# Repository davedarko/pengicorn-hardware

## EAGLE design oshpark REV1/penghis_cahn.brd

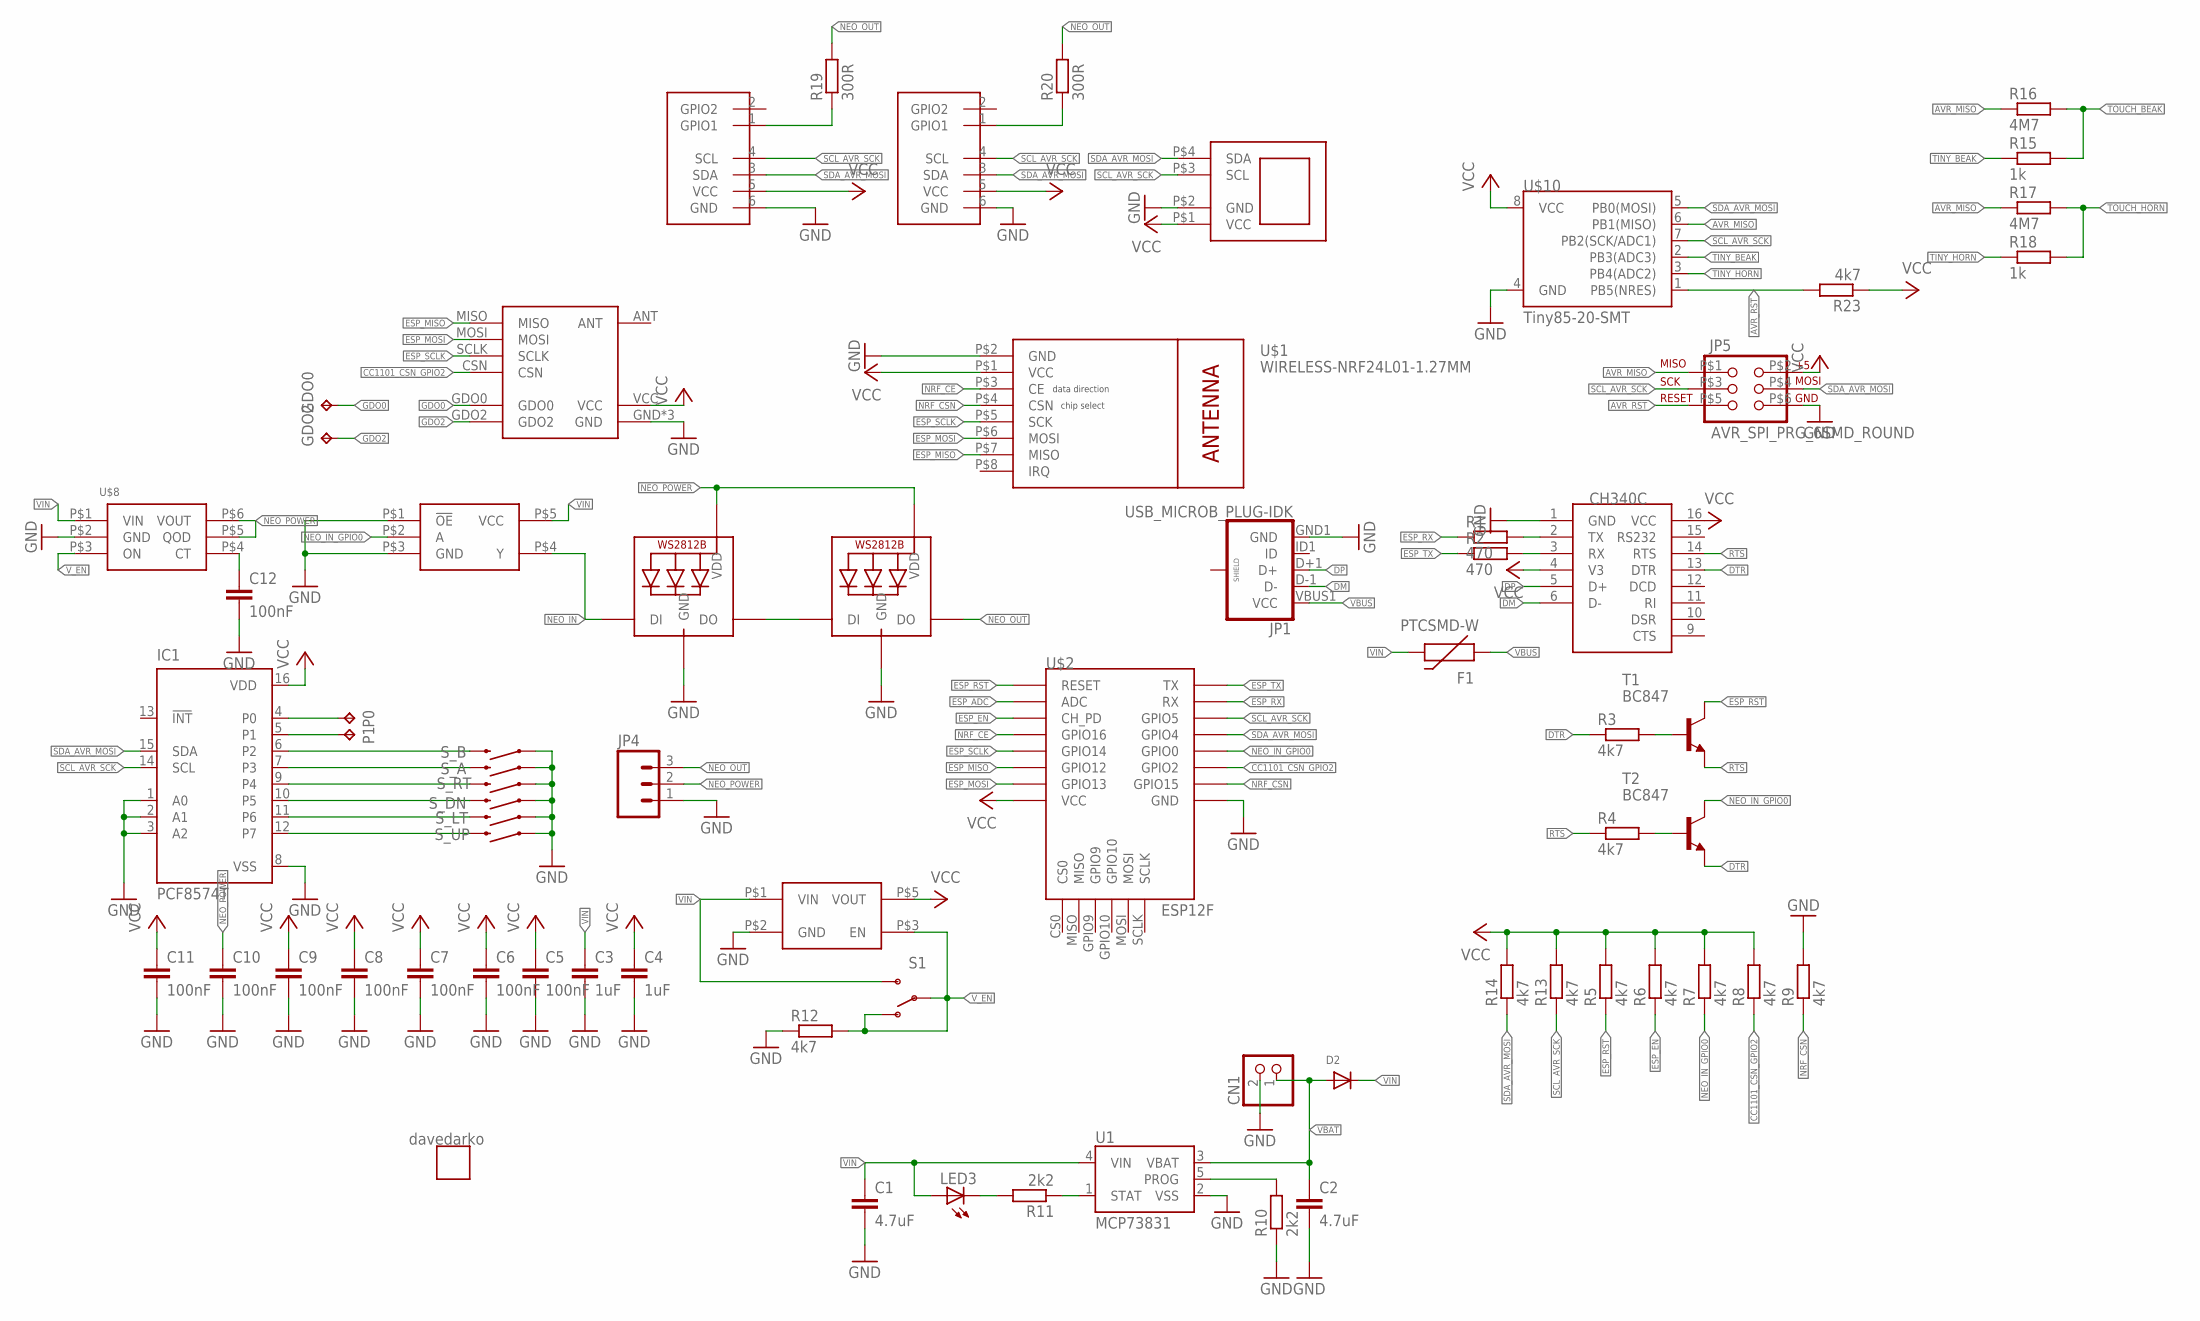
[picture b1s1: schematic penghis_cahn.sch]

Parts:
C1, C2: 4.7uF; C0805
C3, C4: 1uF; C0805
C5, C6, C7, C8, C9, C10, C11, C12: 100nF; C0805
CN1: JST_2PIN-SMT-RA; JST-PH-2-SMT-RA
D2: DIODESOD-123; SOD-123
F1: PTCSMD-W; PTC-1206-WIDE
GDO0, GDO2: TPB1,27; B1,27
IC1: PCF8574T; SO16W
JP1: USB_MICROB_PLUG-IDK; USB-AB-MICRO-SMD_SLOT
JP4: M03LOCK; 1X03_LOCK
JP5: AVR_SPI_PRG_6SMD_ROUND; 2X3_SMD_PAD_ROUND
LED1, LED2: WS2812B5050; WS2812B
LED3: LEDCHIP-LED0603; CHIP-LED0603
P0, P1: TPB1,27; B1,27
R1, R2: 470; R0603
R3, R4, R5, R6, R7, R8, R9, R12, R13, R14, R23: 4k7; R0603
R10, R11: 2k2; R0603
R15, R18: 1k; R0603
R16, R17: 4M7; R0603
R19, R20: 300R; R0603
S1: SWITCH-SPDT-SMD-A; SWITCH-SPST-SMD-A
SAO1, SAO2: SAO-SHITTY-ADDONMASTER; 2X3-KEYED-FEMALE
S_A: SWITCH-MOMENTARY-2-SMD-1101NE; TACTILE-SWITCH-1101NE
S_B: SWITCH-MOMENTARY-2-SMD-1101NE; TACTILE-SWITCH-1101NE
S_DN: SWITCH-MOMENTARY-2-SMD-1101NE; TACTILE-SWITCH-1101NE
S_LT: SWITCH-MOMENTARY-2-SMD-1101NE; TACTILE-SWITCH-1101NE
S_RT: SWITCH-MOMENTARY-2-SMD-1101NE; TACTILE-SWITCH-1101NE
S_UP: SWITCH-MOMENTARY-2-SMD-1101NE; TACTILE-SWITCH-1101NE
T1, T2: BC847; SOT23
U1: MCP73831; SOT23-5
U$1: WIRELESS-NRF24L01-1.27MM
U$2: ESP12F; ESP12PAD
U$3: AP2112KAP2112K; AP2112
U$4: CH340CCH340C; SOIC16
U$5: SN74LV1T125; SN74LV1T125DBVR
U$6: CC1101
U$7: OLED_I2C_VGCD; OLED_1.3
U$8: TPS22917; SOT23
U$9: DAVEDARKODDGOLD; DAVEDARKO_GOLD
U$10: Tiny85-20-SMT; SO08-EIAJ

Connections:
AVR_MISO: JP5.P$1 (1), R16.1, R17.1, U$10.6 (PB1(MISO))
AVR_RST: JP5.P$5 (5), R23.2, U$10.1 (PB5(NRES))
CC1101_CSN_GPIO2: R8.1, U$2.GPIO2, U$6.CSN
DM: JP1.D-1 (D-), U$4.6 (D-)
DP: JP1.D+1 (D+), U$4.5 (D+)
DTR: R3.1, T2.2 (E), U$4.13 (DTR)
ESP_ADC: U$2.ADC
ESP_EN: R6.1, U$2.EN (CH_PD)
ESP_MISO: U$1.P$7 (MISO), U$2.GPIO12, U$6.MISO
ESP_MOSI: U$1.P$6 (MOSI), U$2.GPIO13, U$6.MOSI
ESP_RST: R5.1, T1.3 (C), U$2.RST (RESET)
ESP_RX: R1.1, U$2.RX
ESP_SCLK: U$1.P$5 (SCK), U$2.GPIO14, U$6.SCLK
ESP_TX: R2.1, U$2.TX
GDO0: GDO0.TP, U$6.GDO0
GDO2: GDO2.TP, U$6.GDO2
GND: C1.2, C2.2, C3.2, C4.2, C5.2, C6.2, C7.2, C8.2, C9.2, C10.2, C11.2, C12.2, CN1.2 (1), IC1.1 (A0), IC1.2 (A1), IC1.3 (A2), IC1.8 (VSS), JP1.GND1 (GND), JP4.1, JP5.P$6 (6), LED1.3-GND (GND), LED2.3-GND (GND), R9.2, R10.1, R12.1, SAO1.6 (GND), SAO2.6 (GND), S_A.P$1 (1), S_B.P$1 (1), S_DN.P$1 (1), S_LT.P$1 (1), S_RT.P$1 (1), S_UP.P$1 (1), U1.2 (VSS), U$1.P$2 (GND), U$2.GND, U$3.P$2 (GND), U$4.1 (GND), U$5.P$1 (!OE), U$5.P$3 (GND), U$6.GND, U$6.GND2 (GND), U$6.GND3 (GND), U$7.P$2 (GND), U$8.P$2 (GND), U$10.4 (GND)
unnamed: LED1.2-DOUT (DO), LED2.4-DIN (DI)
unnamed: IC1.12 (P7), S_UP.P$2 (2)
unnamed: IC1.11 (P6), S_LT.P$2 (2)
unnamed: IC1.10 (P5), S_DN.P$2 (2)
unnamed: IC1.9 (P4), S_RT.P$2 (2)
unnamed: R3.2, T1.1 (B)
unnamed: R4.2, T2.1 (B)
unnamed: IC1.7 (P3), S_A.P$2 (2)
unnamed: R19.1, SAO1.1 (GPIO1)
unnamed: R10.2, U1.5 (PROG)
unnamed: R11.1, U1.1 (STAT)
unnamed: R2.2, U$4.3 (RX)
unnamed: R1.2, U$4.2 (TX)
unnamed: IC1.6 (P2), S_B.P$2 (2)
unnamed: LED3.C, R11.2
unnamed: C12.1, U$8.P$4 (CT)
unnamed: R20.1, SAO2.1 (GPIO1)
NEO_IN: LED1.4-DIN (DI), U$5.P$4 (Y)
NEO_IN_GPIO0: R7.1, T2.3 (C), U$2.GPIO0, U$5.P$2 (A)
NEO_OUT: JP4.3, LED2.2-DOUT (DO), R19.2, R20.2
NEO_POWER: C10.1, JP4.2, LED1.1-VDD (VDD), LED2.1-VDD (VDD), U$8.P$5 (QOD), U$8.P$6 (VOUT)
NRF_CE: U$1.P$3 (CE), U$2.GPIO16
NRF_CSN: R9.1, U$1.P$4 (CSN), U$2.GPIO15
P0: IC1.4 (P0), P0.TP
P1: IC1.5 (P1), P1.TP
RTS: R4.1, T1.2 (E), U$4.14 (RTS)
SCL_AVR_SCK: IC1.14 (SCL), JP5.P$3 (3), R13.1, SAO1.4 (SCL), SAO2.4 (SCL), U$2.GPIO5, U$7.P$3 (SCL), U$10.7 (PB2(SCK/ADC1))
SDA_AVR_MOSI: IC1.15 (SDA), JP5.P$4 (4), R14.1, SAO1.3 (SDA), SAO2.3 (SDA), U$2.GPIO4, U$7.P$4 (SDA), U$10.5 (PB0(MOSI))
TINY_BEAK: R15.1, U$10.2 (PB3(ADC3))
TINY_HORN: R18.1, U$10.3 (PB4(ADC2))
TOUCH_BEAK: R15.2, R16.2
TOUCH_HORN: R17.2, R18.2
VBAT: C2.1, CN1.1 (2), D2.A, U1.3 (VBAT)
VBUS: F1.1, JP1.VBUS1 (VCC)
VCC: C4.1, C5.1, C6.1, C7.1, C8.1, C9.1, C11.1, IC1.16 (VDD), JP5.P$2 (2), R5.2, R6.2, R7.2, R8.2, R13.2, R14.2, R23.1, SAO1.5 (VCC), SAO2.5 (VCC), U$1.P$1 (VCC), U$2.VCC, U$3.P$5 (VOUT), U$4.4 (V3), U$4.16 (VCC), U$6.VCC, U$7.P$1 (VCC), U$10.8 (VCC)
VIN: C1.1, C3.1, D2.C, F1.2, LED3.A, S1.3 (S), U1.4 (VIN), U$3.P$1 (VIN), U$5.P$5 (VCC), U$8.P$1 (VIN)
V_EN: R12.2, S1.1 (O), S1.2, U$3.P$3 (EN), U$8.P$3 (ON)

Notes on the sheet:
data direction
chip select

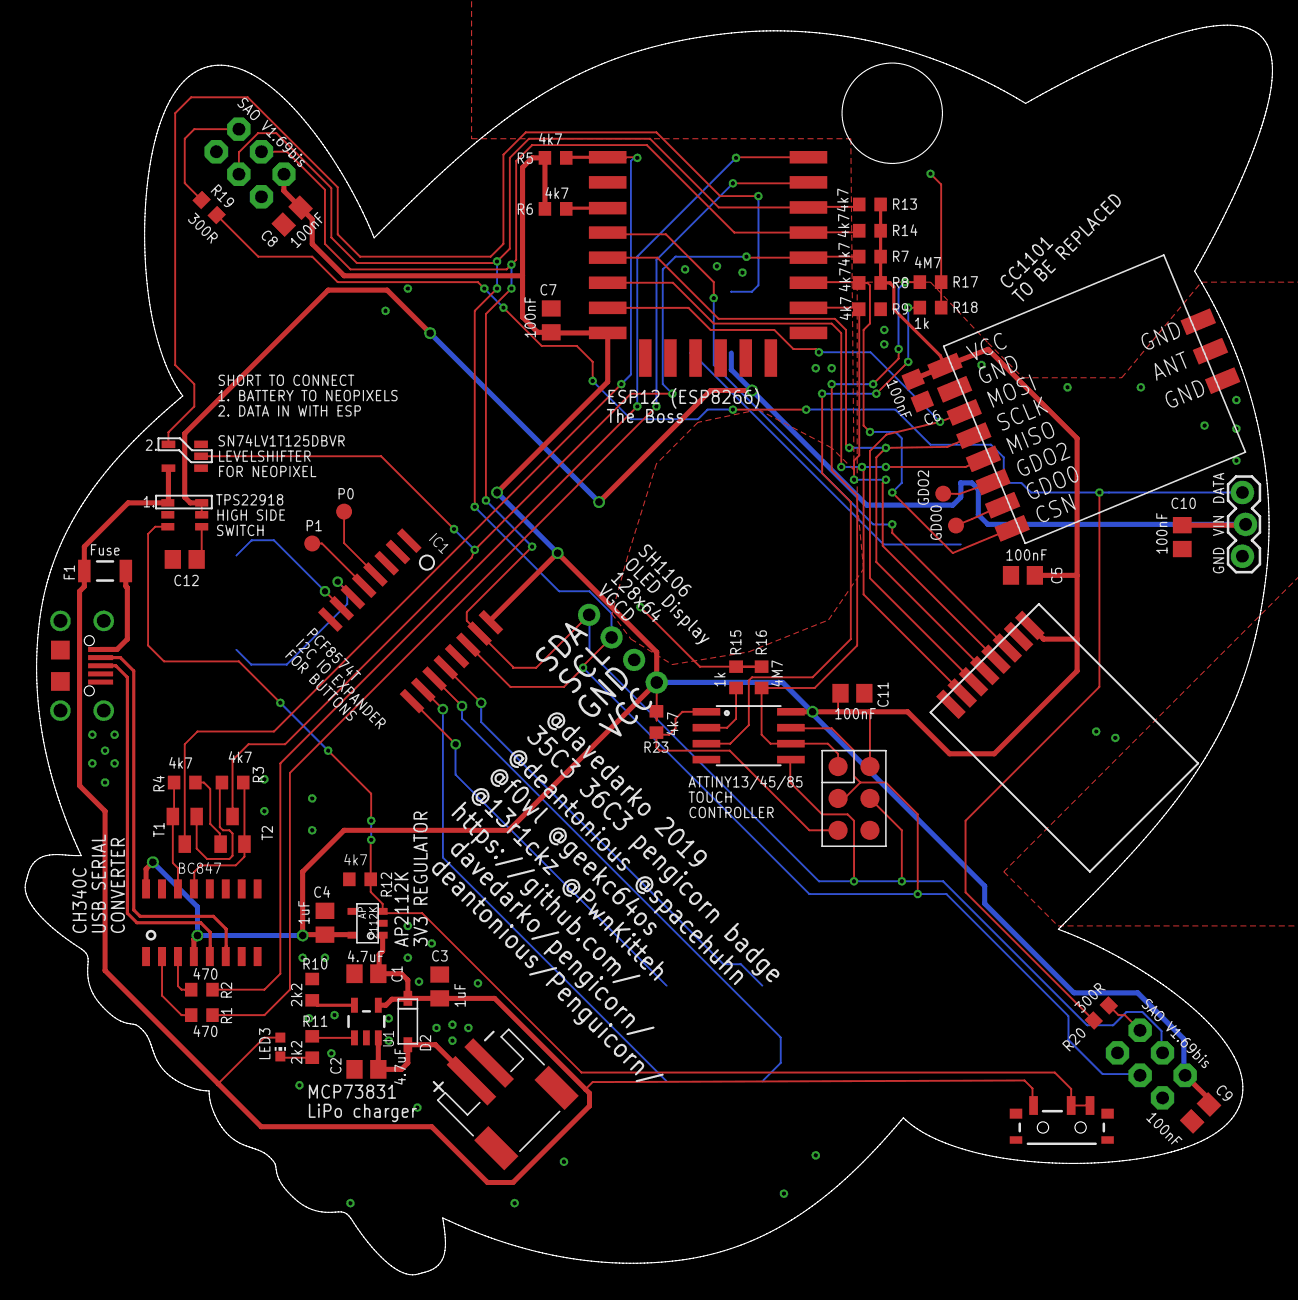
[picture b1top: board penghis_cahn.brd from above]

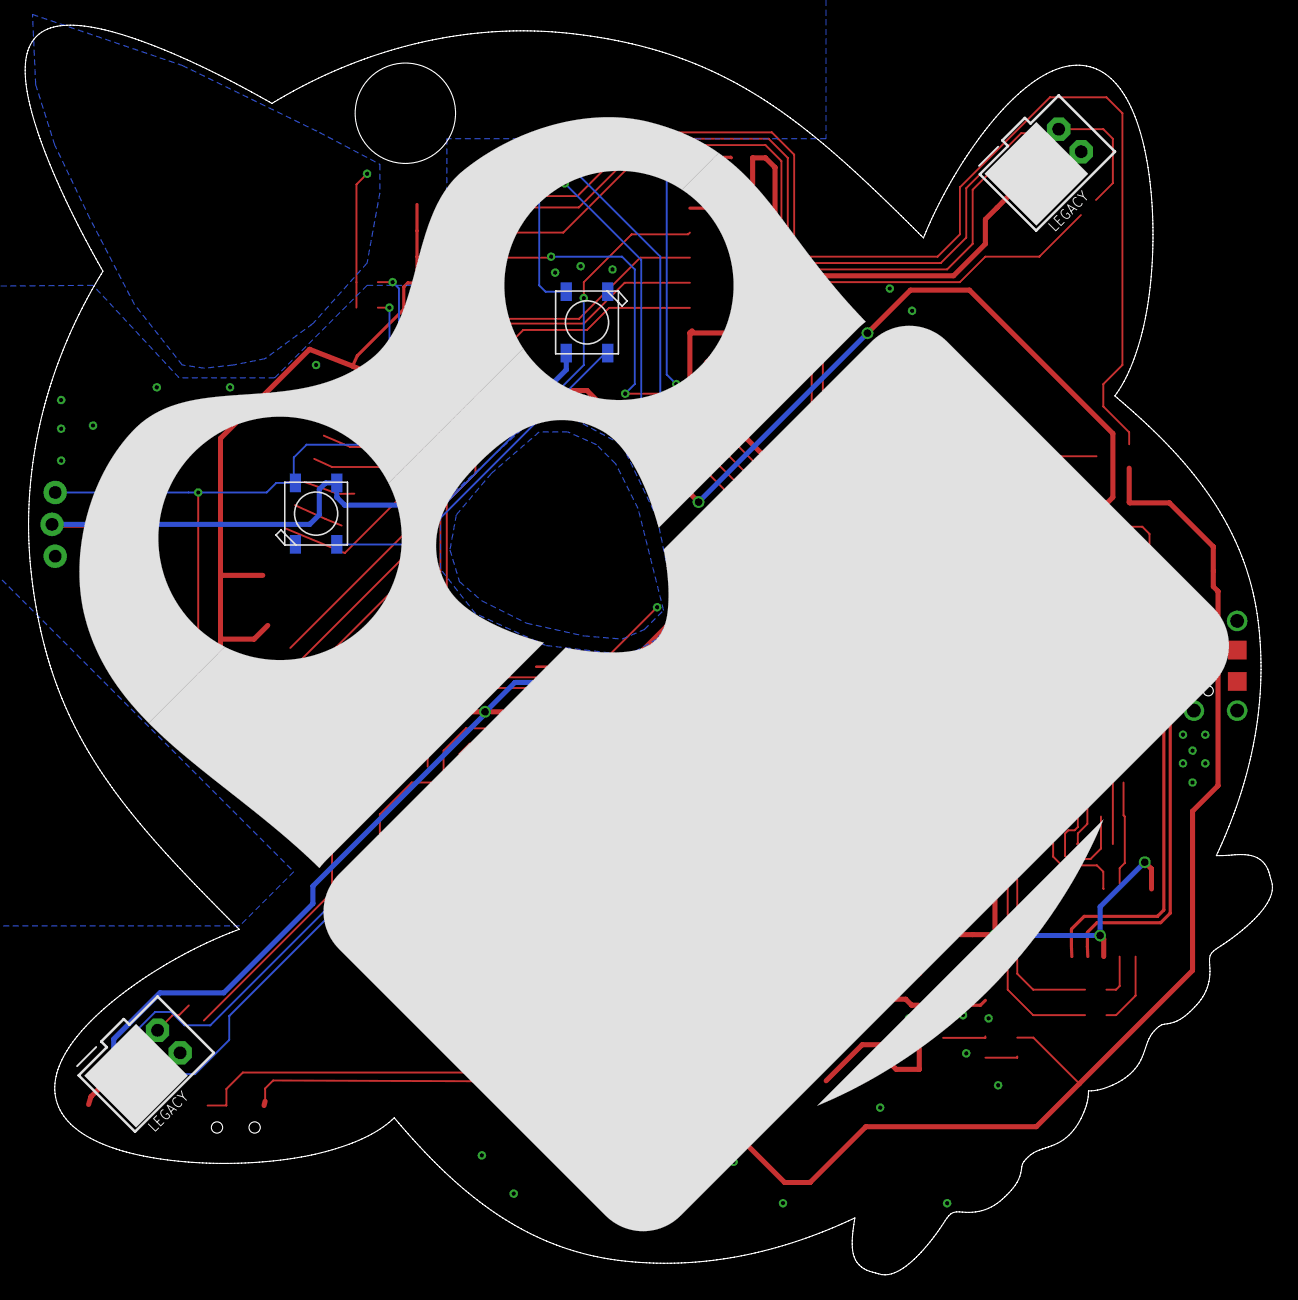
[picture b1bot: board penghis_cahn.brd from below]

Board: 2 copper layers, 99.4 x 99.6 mm, 69 parts (11 on the bottom side), 53 nets.

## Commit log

2018-11-11 design files, gerbers, pdf and bom
2018-11-18 3 versions
2018-12-25 fixed resistor bodge
2019-05-30 minor updates
    added TPS22918 for neopixels
    updated labels
    moved in nrf24 module
    added SAO V1.69bis
2019-05-30 label stuff
2019-05-30 thanks pwn_kitteh
2019-05-30 even more labels
2019-06-01 labels
2020-01-10 changed archive

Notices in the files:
parts and their libraries:
diy-modules: Released under the Creative Commons Attribution 4.0 International License: http://creativecommons.org/licenses/by/4.0
SparkFun-Connectors: Licensing: Creative Commons ShareAlike 4.0 International - https://creativecommons.org/licenses/by-sa/4.0
